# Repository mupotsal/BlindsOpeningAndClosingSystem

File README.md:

# BlindsOpeningAndClosingSystem

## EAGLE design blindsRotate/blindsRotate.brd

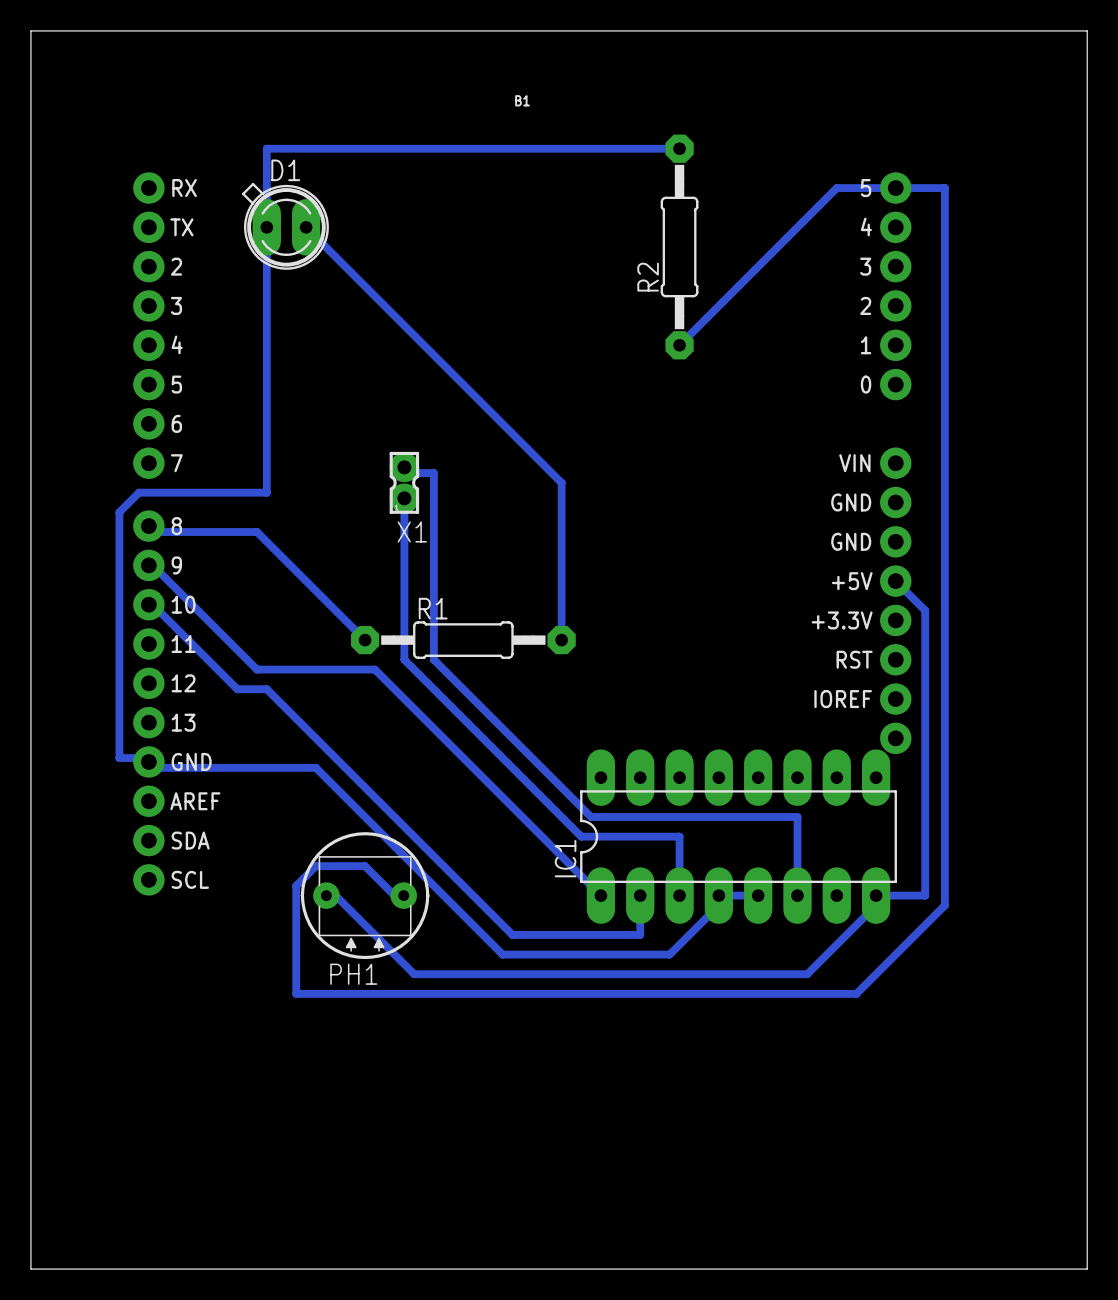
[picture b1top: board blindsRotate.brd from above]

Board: 2 copper layers, 68.2 x 80.0 mm, 7 parts (0 on the bottom side), 10 nets.

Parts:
B1: ARDUINO_UNO_R3_SHIELDBASIC; UNO_R3_SHIELD
D1: SFH482
IC1: L293D; DIL16
PH1: D1160_12; D11XX
R1, R2: 0207/12
X1: 332-02

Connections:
unnamed: B1.D8, R1.1
unnamed: D1.K, R1.2
unnamed: B1.D9, IC1.1
unnamed: B1.D10, IC1.2
unnamed: IC1.3, X1.1
unnamed: IC1.6, X1.2
unnamed: B1.D11, IC1.7
unnamed: B1.A5, PH1.2, R2.1
unnamed: B1.5V, IC1.8, PH1.1
unnamed: B1.GND@2, D1.A, IC1.4, IC1.5, R2.2

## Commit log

2021-12-02 adding schmatic
2021-12-02 added extension
2021-12-02 Add folder for code

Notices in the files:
parts and their libraries:
SparkFun-Boards: Licensing: Creative Commons ShareAlike 4.0 International - https://creativecommons.org/licenses/by-sa/4.0
